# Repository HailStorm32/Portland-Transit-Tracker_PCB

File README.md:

Info
=========
These are the PCB files for the custom PCB that shows in real time what TriMet MAX stations have a train at them. Details regarding the code can be found <a href="https://github.com/HailStorm32/Portland-Transit-Tracker_Code">here</a>. More detail into how this was made, can be found <a href="https://www.vsickle.net/projects/trimet-transit-tracker.html">here</a>

V1 and V2.1 were both designed in Eagle. V2.1 is the version that was actually produced. 

For V2.1, the board was manufactuerd through <a href="https://jlcpcb.com/">JLCPCB</a>, and I solderd all the SMD componets.

## Bill of Materials for V2.1
</img>

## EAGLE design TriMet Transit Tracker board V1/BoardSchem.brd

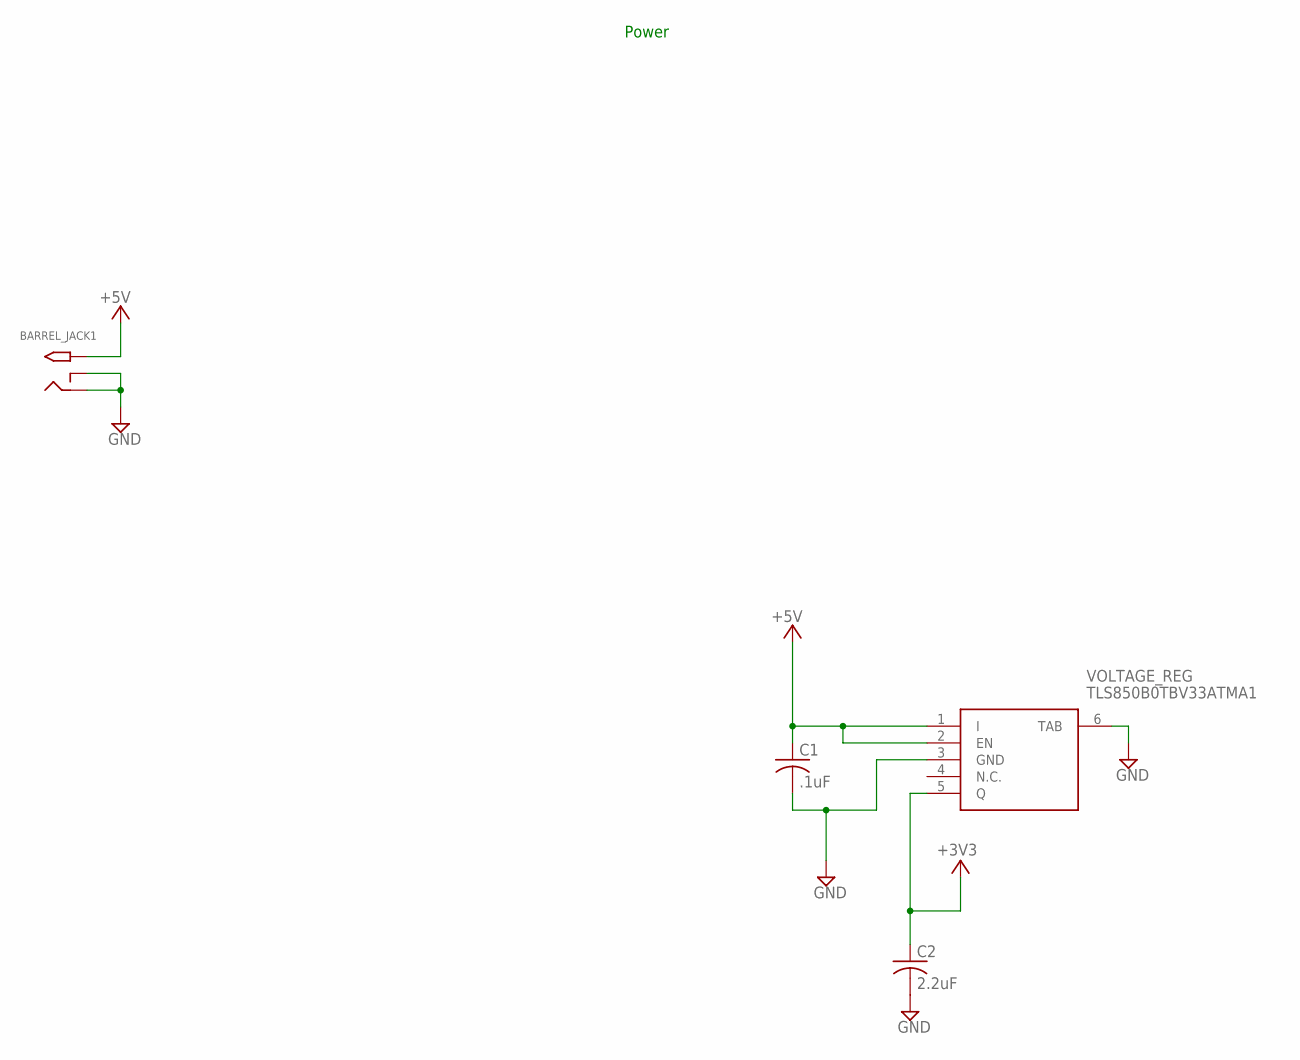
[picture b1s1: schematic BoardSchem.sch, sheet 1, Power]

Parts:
BARREL_JACK1: 2.1MMJACKTHM; PJ-102A
C1: .1uF; C0805
C2: 2.2uF; C0805
VOLTAGE_REG: TLS850B0TBV33ATMA1

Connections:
+3V3: C2.1, VOLTAGE_REG.5 (Q); also elsewhere on the board
+5V: BARREL_JACK1.TIP, C1.1, VOLTAGE_REG.1 (I), VOLTAGE_REG.2 (EN); also elsewhere on the board
GND: BARREL_JACK1.RING, BARREL_JACK1.RING_SW, C1.2, C2.2, VOLTAGE_REG.3 (GND), VOLTAGE_REG.6 (TAB); also elsewhere on the board

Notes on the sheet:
Power

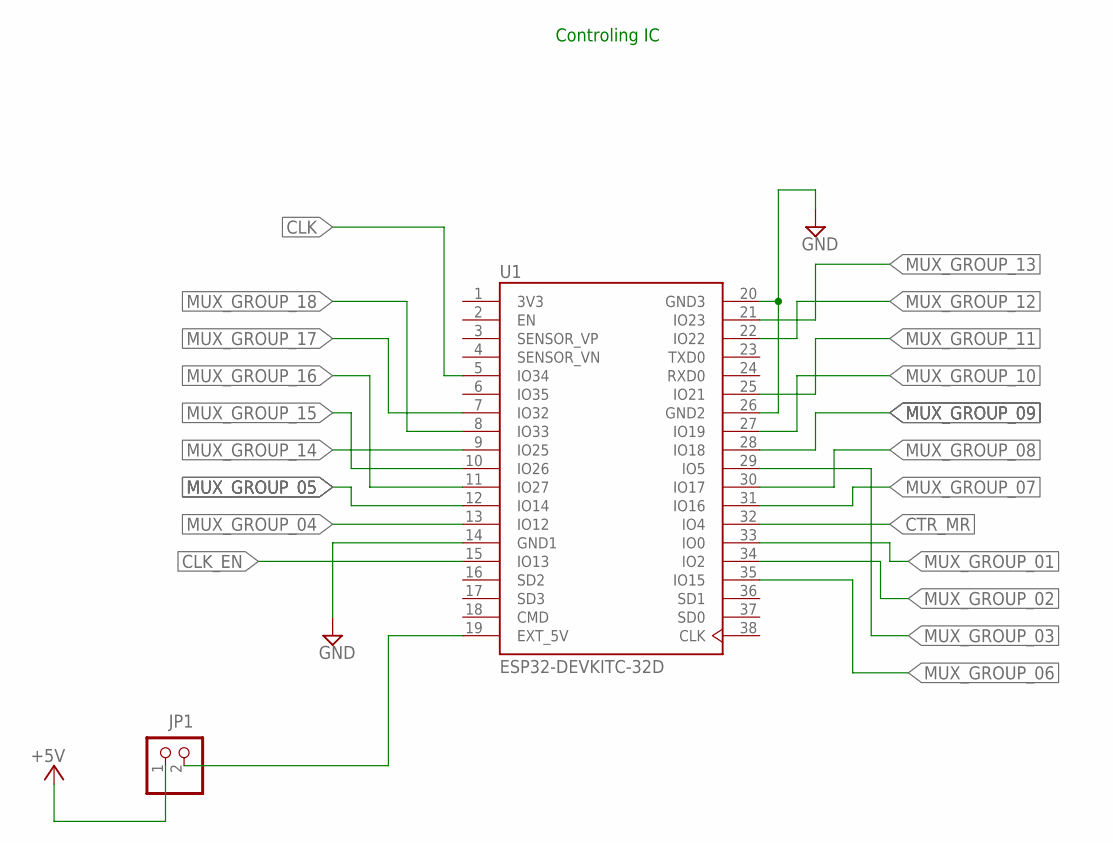
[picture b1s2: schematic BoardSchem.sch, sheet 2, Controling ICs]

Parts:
JP1: PINHD-1X2; 1X02
U1: ESP32-DEVKITC-32D; MODULE_ESP32-DEVKITC-32D

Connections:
3V3: U1.1 (3V3)
+5V: JP1.1; also elsewhere on the board
CLK: U1.5 (IO34); also elsewhere on the board
CLK_EN: U1.15 (IO13); also elsewhere on the board
CTR_MR: U1.32 (IO4); also elsewhere on the board
GND: U1.14 (GND1), U1.20 (GND3), U1.26 (GND2); also elsewhere on the board
MUX_GROUP_01: U1.33 (IO0); also elsewhere on the board
MUX_GROUP_02: U1.34 (IO2); also elsewhere on the board
MUX_GROUP_03: U1.29 (IO5); also elsewhere on the board
MUX_GROUP_04: U1.13 (IO12); also elsewhere on the board
MUX_GROUP_05: U1.12 (IO14); also elsewhere on the board
MUX_GROUP_06: U1.35 (IO15); also elsewhere on the board
MUX_GROUP_07: U1.31 (IO16); also elsewhere on the board
MUX_GROUP_08: U1.30 (IO17); also elsewhere on the board
MUX_GROUP_09: U1.28 (IO18); also elsewhere on the board
MUX_GROUP_10: U1.27 (IO19); also elsewhere on the board
MUX_GROUP_11: U1.25 (IO21); also elsewhere on the board
MUX_GROUP_12: U1.22 (IO22); also elsewhere on the board
MUX_GROUP_13: U1.21 (IO23); also elsewhere on the board
MUX_GROUP_14: U1.9 (IO25); also elsewhere on the board
MUX_GROUP_15: U1.10 (IO26); also elsewhere on the board
MUX_GROUP_16: U1.11 (IO27); also elsewhere on the board
MUX_GROUP_17: U1.7 (IO32); also elsewhere on the board
MUX_GROUP_18: U1.8 (IO33); also elsewhere on the board
unnamed: JP1.2, U1.19 (EXT_5V)

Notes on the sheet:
Controling IC

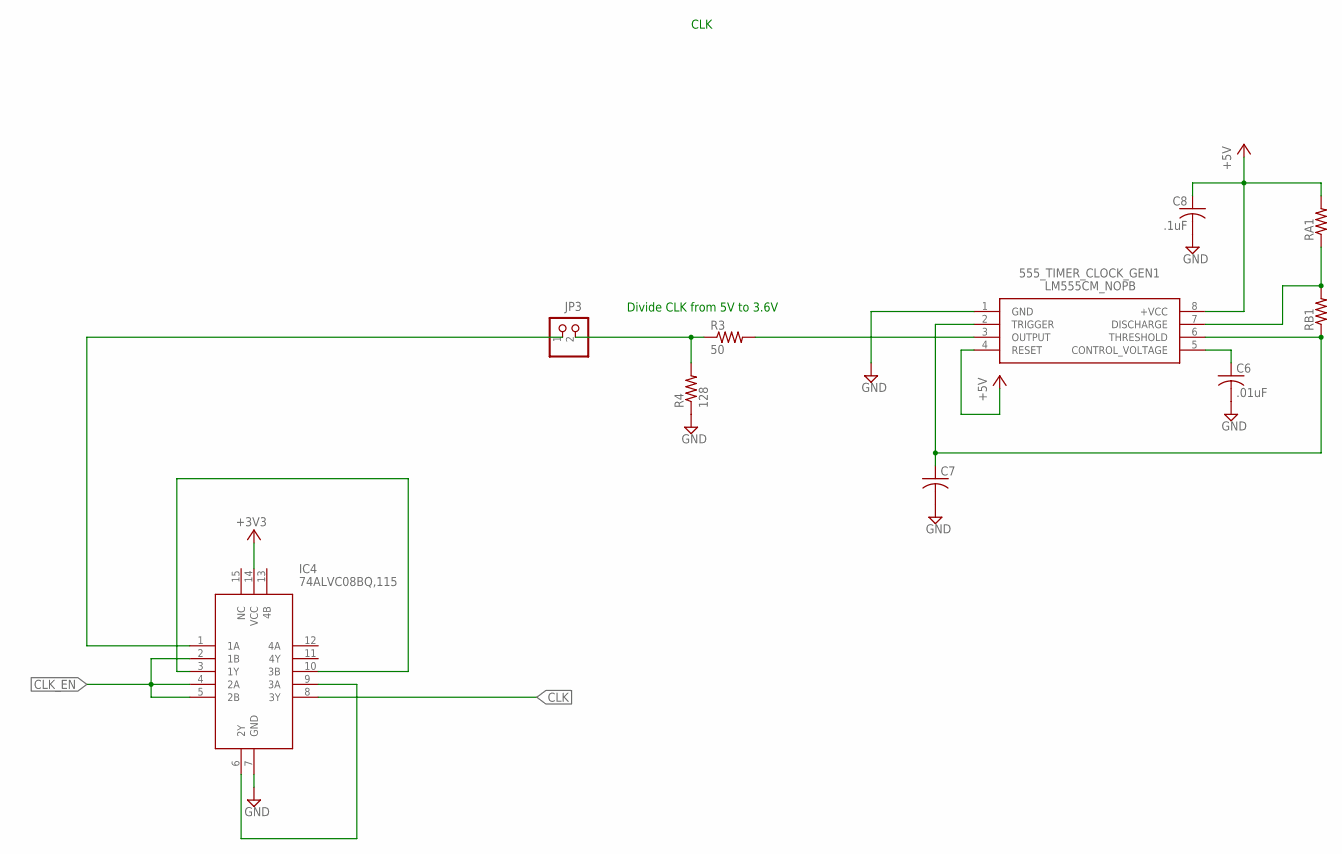
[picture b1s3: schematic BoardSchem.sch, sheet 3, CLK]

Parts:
555_TIMER_CLOCK_GEN1: LM555CM_NOPB; SOIC127P600X175-8N
C6: .01uF; C0805
C7: C-USC0805; C0805
C8: .1uF; C0805
IC4: 74ALVC08BQ,115; QFN50P250X300X100-15N
JP3: PINHD-1X2; 1X02
R3: 50; R0805
R4: 128; R0805
RA1: R-US_R0805; R0805
RB1: R-US_R0805; R0805

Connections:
+3V3: IC4.14 (VCC); also elsewhere on the board
+5V: 555_TIMER_CLOCK_GEN1.4 (RESET), 555_TIMER_CLOCK_GEN1.8 (+VCC), C8.1, RA1.2; also elsewhere on the board
CLK: IC4.8 (3Y); also elsewhere on the board
CLK_EN: IC4.2 (1B), IC4.4 (2A), IC4.5 (2B); also elsewhere on the board
GND: 555_TIMER_CLOCK_GEN1.1 (GND), C6.2, C7.2, C8.2, IC4.7 (GND), R4.1; also elsewhere on the board
unnamed: JP3.2, R3.1, R4.2
unnamed: 555_TIMER_CLOCK_GEN1.5 (CONTROL_VOLTAGE), C6.1
unnamed: 555_TIMER_CLOCK_GEN1.3 (OUTPUT), R3.2
unnamed: 555_TIMER_CLOCK_GEN1.2 (TRIGGER), 555_TIMER_CLOCK_GEN1.6 (THRESHOLD), C7.1, RB1.1
unnamed: 555_TIMER_CLOCK_GEN1.7 (DISCHARGE), RA1.1, RB1.2
unnamed: IC4.1 (1A), JP3.1
unnamed: IC4.6 (2Y), IC4.9 (3A)
unnamed: IC4.3 (1Y), IC4.10 (3B)

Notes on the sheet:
Divide CLK from 5V to 3.6V
CLK

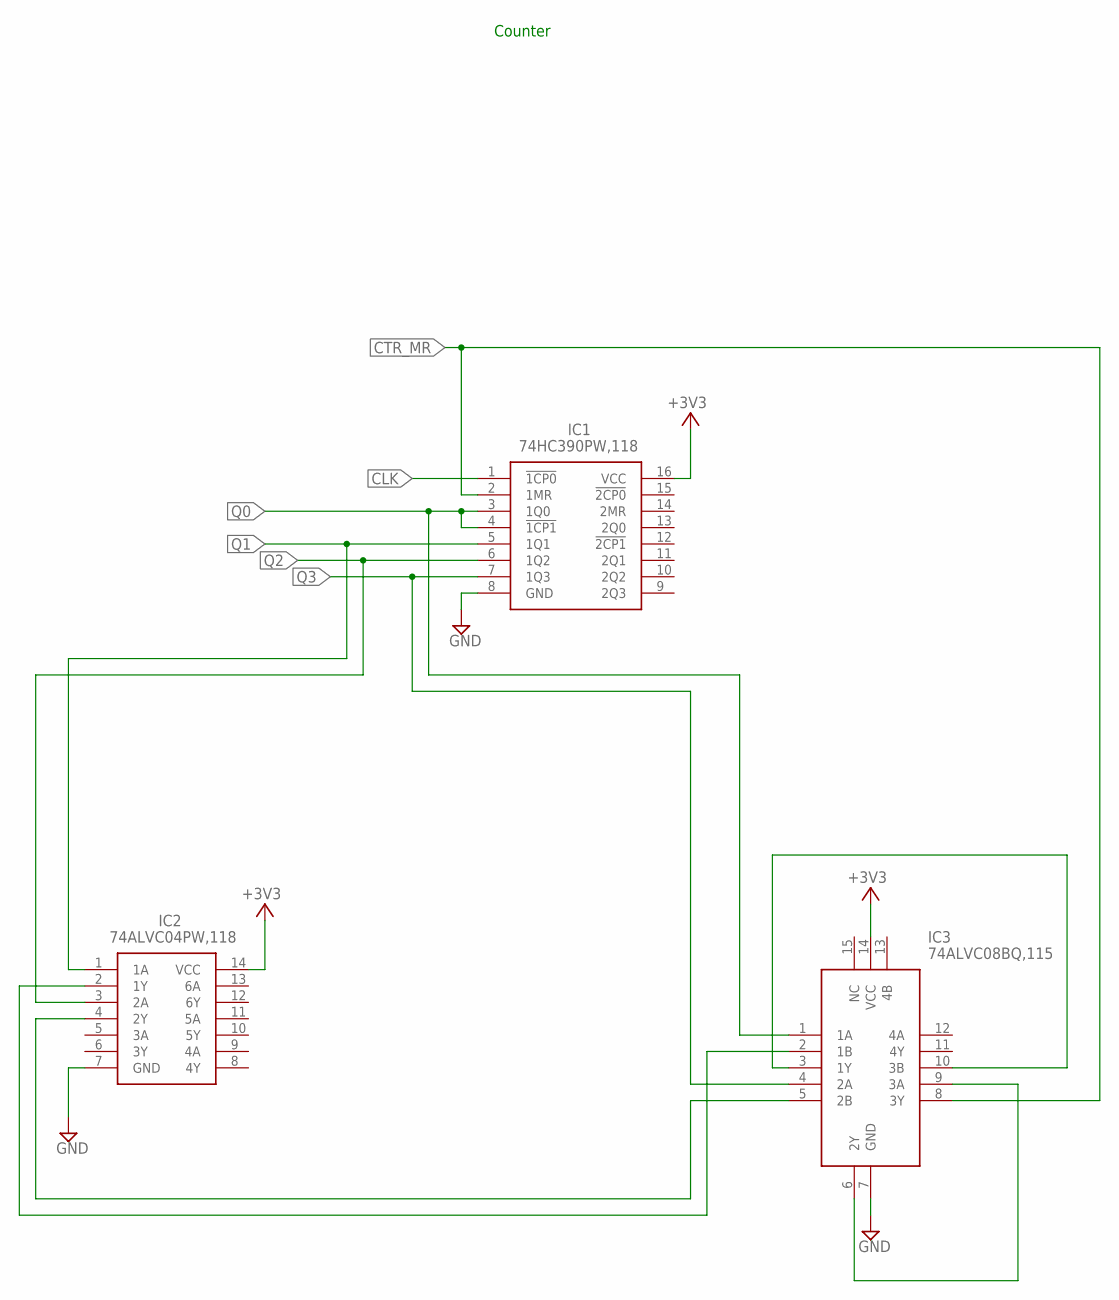
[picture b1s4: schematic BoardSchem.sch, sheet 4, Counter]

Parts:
IC1: 74HC390PW,118; SOP65P640X110-16N
IC2: 74ALVC04PW,118; SOP65P640X110-14N
IC3: 74ALVC08BQ,115; QFN50P250X300X100-15N

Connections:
+3V3: IC1.16 (VCC), IC2.14 (VCC), IC3.14 (VCC); also elsewhere on the board
CLK: IC1.1 (!1CP0); also elsewhere on the board
CTR_MR: IC1.2 (1MR), IC3.8 (3Y); also elsewhere on the board
GND: IC1.8 (GND), IC2.7 (GND), IC3.7 (GND); also elsewhere on the board
unnamed: IC2.4 (2Y), IC3.5 (2B)
unnamed: IC3.3 (1Y), IC3.10 (3B)
unnamed: IC2.2 (1Y), IC3.2 (1B)
unnamed: IC3.6 (2Y), IC3.9 (3A)
Q0: IC1.3 (1Q0), IC1.4 (!1CP1), IC3.1 (1A); also elsewhere on the board
Q1: IC1.5 (1Q1), IC2.1 (1A); also elsewhere on the board
Q2: IC1.6 (1Q2), IC2.3 (2A); also elsewhere on the board
Q3: IC1.7 (1Q3), IC3.4 (2A)

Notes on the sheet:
Counter

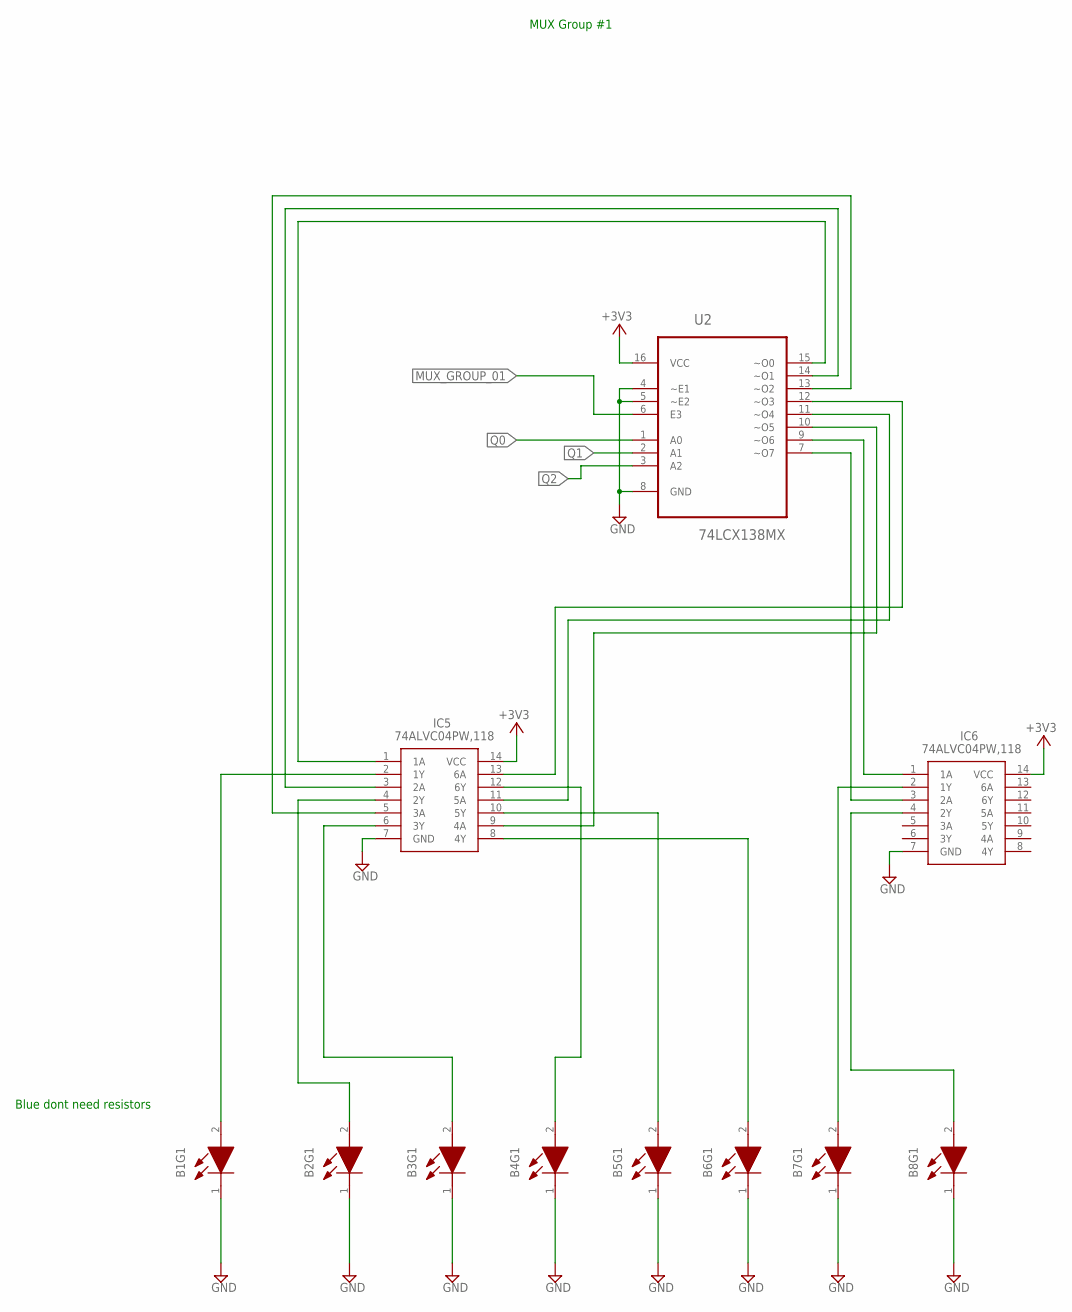
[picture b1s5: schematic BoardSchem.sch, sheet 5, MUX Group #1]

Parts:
B1G1, B2G1, B3G1, B4G1, B5G1, B6G1, B7G1, B8G1: LTST-C170TBKT; LEDC2012X120N
IC5, IC6: 74ALVC04PW,118; SOP65P640X110-14N
U2: 74LCX138MX; SOIC127P600X175-16N

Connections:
+3V3: IC5.14 (VCC), IC6.14 (VCC), U2.16 (VCC); also elsewhere on the board
GND: B1G1.1 (K), B2G1.1 (K), B3G1.1 (K), B4G1.1 (K), B5G1.1 (K), B6G1.1 (K), B7G1.1 (K), B8G1.1 (K), IC5.7 (GND), IC6.7 (GND), U2.4 (~E1), U2.5 (~E2), U2.8 (GND); also elsewhere on the board
MUX_GROUP_01: U2.6 (E3); also elsewhere on the board
unnamed: IC5.1 (1A), U2.15 (~O0)
unnamed: B1G1.2 (A), IC5.2 (1Y)
unnamed: IC5.3 (2A), U2.14 (~O1)
unnamed: B2G1.2 (A), IC5.4 (2Y)
unnamed: IC5.5 (3A), U2.13 (~O2)
unnamed: B3G1.2 (A), IC5.6 (3Y)
unnamed: IC5.13 (6A), U2.12 (~O3)
unnamed: B4G1.2 (A), IC5.12 (6Y)
unnamed: IC5.11 (5A), U2.11 (~O4)
unnamed: B5G1.2 (A), IC5.10 (5Y)
unnamed: IC5.9 (4A), U2.10 (~O5)
unnamed: B6G1.2 (A), IC5.8 (4Y)
unnamed: IC6.1 (1A), U2.9 (~O6)
unnamed: B7G1.2 (A), IC6.2 (1Y)
unnamed: IC6.3 (2A), U2.7 (~O7)
unnamed: B8G1.2 (A), IC6.4 (2Y)
Q0: U2.1 (A0); also elsewhere on the board
Q1: U2.2 (A1); also elsewhere on the board
Q2: U2.3 (A2); also elsewhere on the board

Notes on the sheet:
Blue dont need resistors
MUX Group #1

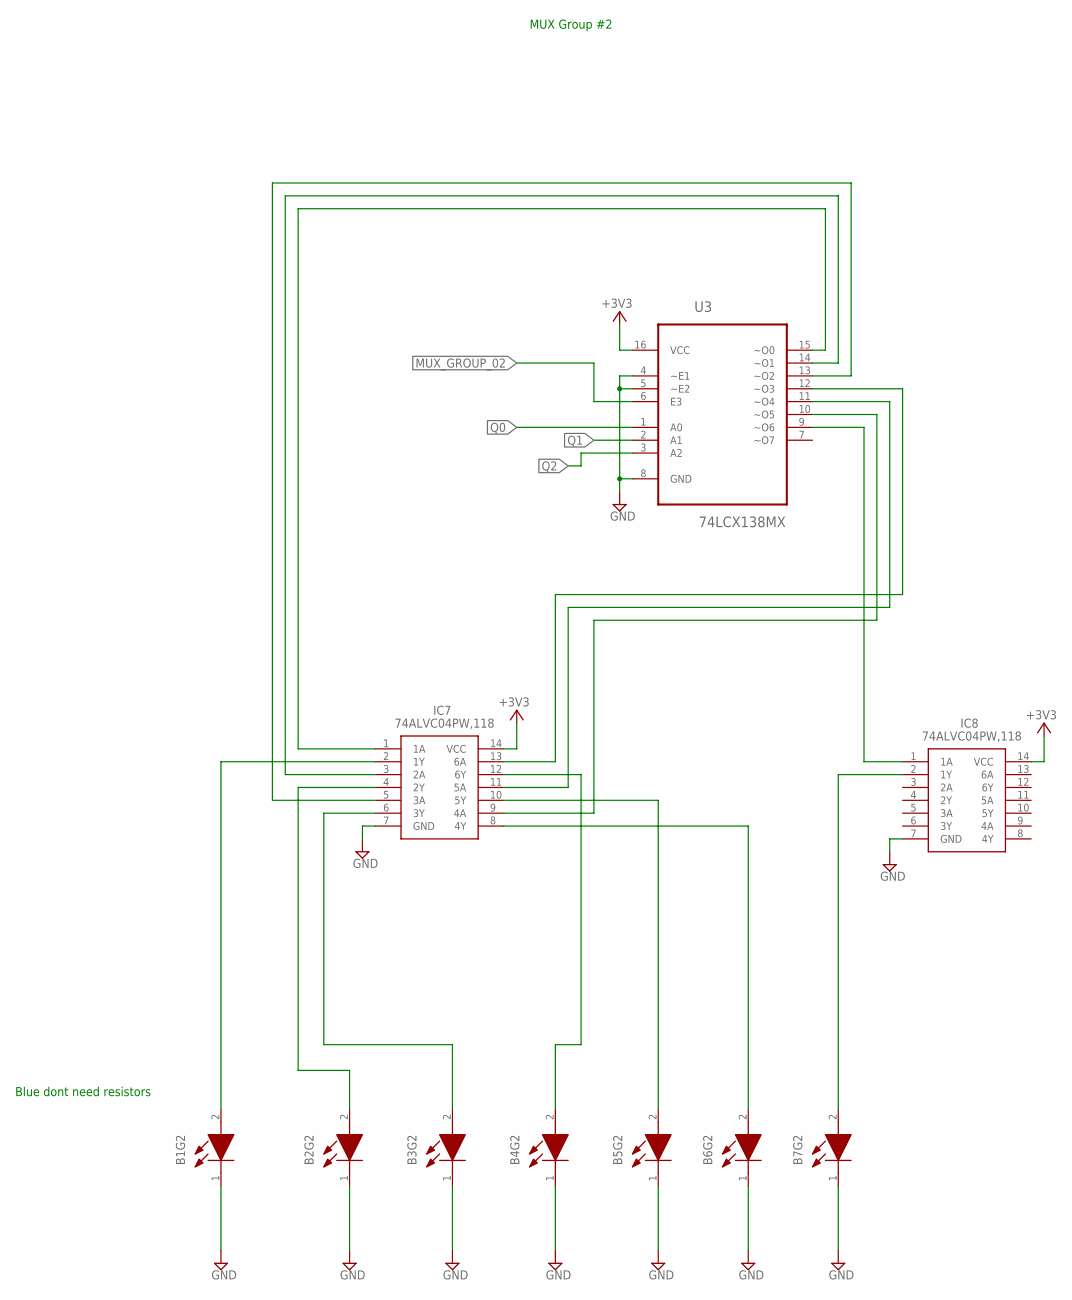
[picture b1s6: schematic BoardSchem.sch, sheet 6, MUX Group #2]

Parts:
B1G2, B2G2, B3G2, B4G2, B5G2, B6G2, B7G2: LTST-C170TBKT; LEDC2012X120N
IC7, IC8: 74ALVC04PW,118; SOP65P640X110-14N
U3: 74LCX138MX; SOIC127P600X175-16N

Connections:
+3V3: IC7.14 (VCC), IC8.14 (VCC), U3.16 (VCC); also elsewhere on the board
GND: B1G2.1 (K), B2G2.1 (K), B3G2.1 (K), B4G2.1 (K), B5G2.1 (K), B6G2.1 (K), B7G2.1 (K), IC7.7 (GND), IC8.7 (GND), U3.4 (~E1), U3.5 (~E2), U3.8 (GND); also elsewhere on the board
MUX_GROUP_02: U3.6 (E3); also elsewhere on the board
unnamed: IC7.1 (1A), U3.15 (~O0)
unnamed: B1G2.2 (A), IC7.2 (1Y)
unnamed: IC7.3 (2A), U3.14 (~O1)
unnamed: B2G2.2 (A), IC7.4 (2Y)
unnamed: IC7.5 (3A), U3.13 (~O2)
unnamed: B3G2.2 (A), IC7.6 (3Y)
unnamed: IC7.13 (6A), U3.12 (~O3)
unnamed: B4G2.2 (A), IC7.12 (6Y)
unnamed: IC7.11 (5A), U3.11 (~O4)
unnamed: B5G2.2 (A), IC7.10 (5Y)
unnamed: IC7.9 (4A), U3.10 (~O5)
unnamed: B6G2.2 (A), IC7.8 (4Y)
unnamed: IC8.1 (1A), U3.9 (~O6)
unnamed: B7G2.2 (A), IC8.2 (1Y)
Q0: U3.1 (A0); also elsewhere on the board
Q1: U3.2 (A1); also elsewhere on the board
Q2: U3.3 (A2); also elsewhere on the board

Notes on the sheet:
Blue dont need resistors
MUX Group #2

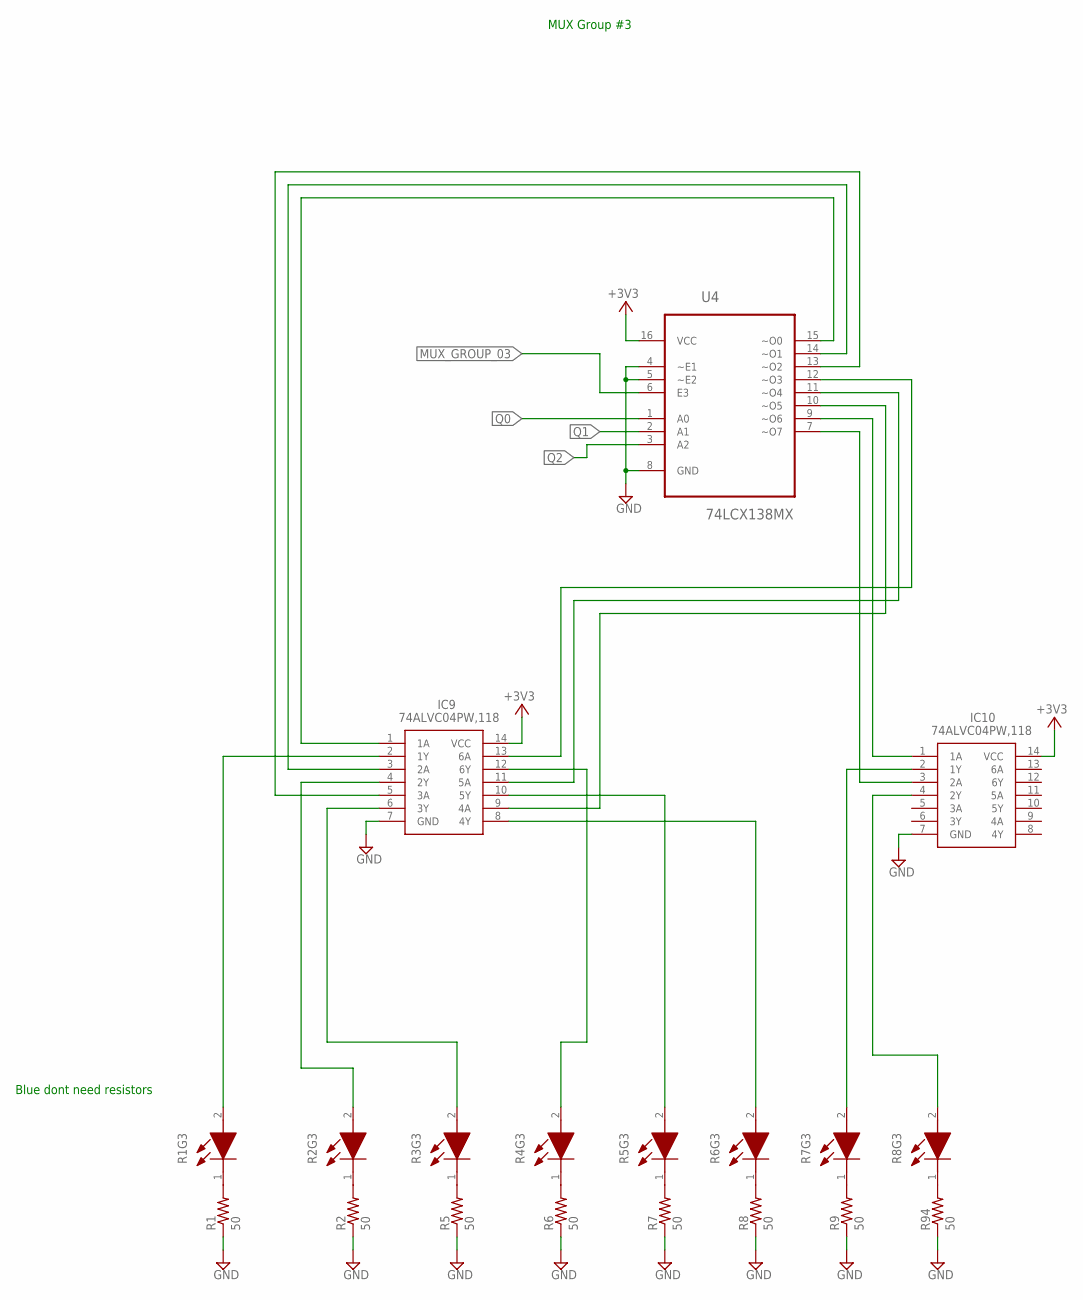
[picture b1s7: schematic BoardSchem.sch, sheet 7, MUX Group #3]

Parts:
IC9, IC10: 74ALVC04PW,118; SOP65P640X110-14N
R1, R2, R5, R6, R7, R8, R9, R94: 50; R0805
R1G3, R2G3, R3G3, R4G3, R5G3, R6G3, R7G3, R8G3: LTST-C170TBKT; LEDC2012X120N
U4: 74LCX138MX; SOIC127P600X175-16N

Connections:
+3V3: IC9.14 (VCC), IC10.14 (VCC), U4.16 (VCC); also elsewhere on the board
GND: IC9.7 (GND), IC10.7 (GND), R1.1, R2.1, R5.1, R6.1, R7.1, R8.1, R9.1, R94.1, U4.4 (~E1), U4.5 (~E2), U4.8 (GND); also elsewhere on the board
MUX_GROUP_03: U4.6 (E3); also elsewhere on the board
unnamed: IC10.3 (2A), U4.7 (~O7)
unnamed: R1.2, R1G3.1 (K)
unnamed: R2.2, R2G3.1 (K)
unnamed: R8G3.1 (K), R94.2
unnamed: IC9.1 (1A), U4.15 (~O0)
unnamed: IC9.2 (1Y), R1G3.2 (A)
unnamed: IC9.3 (2A), U4.14 (~O1)
unnamed: IC9.4 (2Y), R2G3.2 (A)
unnamed: IC9.5 (3A), U4.13 (~O2)
unnamed: IC9.6 (3Y), R3G3.2 (A)
unnamed: IC9.13 (6A), U4.12 (~O3)
unnamed: IC9.12 (6Y), R4G3.2 (A)
unnamed: IC9.11 (5A), U4.11 (~O4)
unnamed: IC9.10 (5Y), R5G3.2 (A)
unnamed: IC9.9 (4A), U4.10 (~O5)
unnamed: IC9.8 (4Y), R6G3.2 (A)
unnamed: IC10.1 (1A), U4.9 (~O6)
unnamed: IC10.2 (1Y), R7G3.2 (A)
unnamed: R3G3.1 (K), R5.2
unnamed: R4G3.1 (K), R6.2
unnamed: IC10.4 (2Y), R8G3.2 (A)
unnamed: R5G3.1 (K), R7.2
unnamed: R6G3.1 (K), R8.2
unnamed: R7G3.1 (K), R9.2
Q0: U4.1 (A0); also elsewhere on the board
Q1: U4.2 (A1); also elsewhere on the board
Q2: U4.3 (A2); also elsewhere on the board

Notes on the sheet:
Blue dont need resistors
MUX Group #3

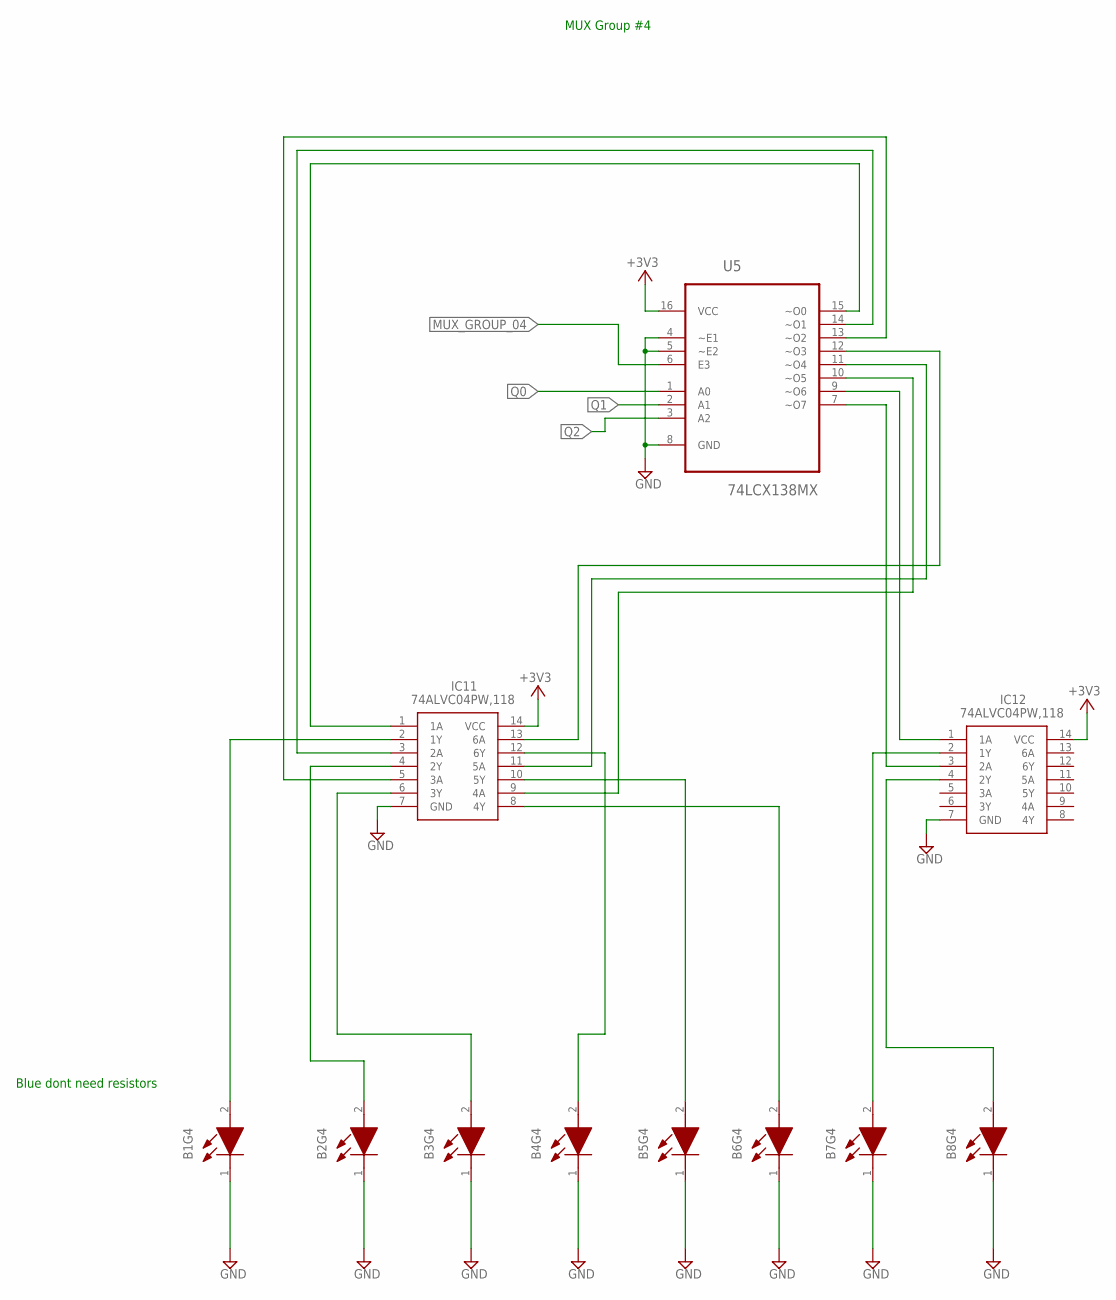
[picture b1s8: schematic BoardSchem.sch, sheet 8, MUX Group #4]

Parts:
B1G4, B2G4, B3G4, B4G4, B5G4, B6G4, B7G4, B8G4: LTST-C170TBKT; LEDC2012X120N
IC11, IC12: 74ALVC04PW,118; SOP65P640X110-14N
U5: 74LCX138MX; SOIC127P600X175-16N

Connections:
+3V3: IC11.14 (VCC), IC12.14 (VCC), U5.16 (VCC); also elsewhere on the board
GND: B1G4.1 (K), B2G4.1 (K), B3G4.1 (K), B4G4.1 (K), B5G4.1 (K), B6G4.1 (K), B7G4.1 (K), B8G4.1 (K), IC11.7 (GND), IC12.7 (GND), U5.4 (~E1), U5.5 (~E2), U5.8 (GND); also elsewhere on the board
MUX_GROUP_04: U5.6 (E3); also elsewhere on the board
unnamed: IC11.1 (1A), U5.15 (~O0)
unnamed: B1G4.2 (A), IC11.2 (1Y)
unnamed: IC11.3 (2A), U5.14 (~O1)
unnamed: B2G4.2 (A), IC11.4 (2Y)
unnamed: IC11.5 (3A), U5.13 (~O2)
unnamed: B3G4.2 (A), IC11.6 (3Y)
unnamed: IC11.13 (6A), U5.12 (~O3)
unnamed: B4G4.2 (A), IC11.12 (6Y)
unnamed: IC11.11 (5A), U5.11 (~O4)
unnamed: B5G4.2 (A), IC11.10 (5Y)
unnamed: IC11.9 (4A), U5.10 (~O5)
unnamed: B6G4.2 (A), IC11.8 (4Y)
unnamed: IC12.1 (1A), U5.9 (~O6)
unnamed: B7G4.2 (A), IC12.2 (1Y)
unnamed: IC12.3 (2A), U5.7 (~O7)
unnamed: B8G4.2 (A), IC12.4 (2Y)
Q0: U5.1 (A0); also elsewhere on the board
Q1: U5.2 (A1); also elsewhere on the board
Q2: U5.3 (A2); also elsewhere on the board

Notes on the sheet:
Blue dont need resistors
MUX Group #4

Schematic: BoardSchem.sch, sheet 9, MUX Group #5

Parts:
B1G5, B2G5, B3G5, B4G5: LTST-C170TBKT; LEDC2012X120N
G6G5, G7G5, G8G5: LTST-C170TBKT; LEDC2012X120N
IC13, IC14: 74ALVC04PW,118; SOP65P640X110-14N
R5G5: LTST-C170TBKT; LEDC2012X120N
R10, R11, R12, R13: 50; R0805
U6: 74LCX138MX; SOIC127P600X175-16N

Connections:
+3V3: IC13.14 (VCC), IC14.14 (VCC), U6.16 (VCC); also elsewhere on the board
GND: B1G5.1 (K), B2G5.1 (K), B3G5.1 (K), B4G5.1 (K), IC13.7 (GND), IC14.7 (GND), R10.1, R11.1, R12.1, R13.1, U6.4 (~E1), U6.5 (~E2), U6.8 (GND); also elsewhere on the board
MUX_GROUP_05: U6.6 (E3); also elsewhere on the board
unnamed: IC13.1 (1A), U6.15 (~O0)
unnamed: B1G5.2 (A), IC13.2 (1Y)
unnamed: IC13.3 (2A), U6.14 (~O1)
unnamed: B2G5.2 (A), IC13.4 (2Y)
unnamed: IC13.5 (3A), U6.13 (~O2)
unnamed: B3G5.2 (A), IC13.6 (3Y)
unnamed: IC13.13 (6A), U6.12 (~O3)
unnamed: B4G5.2 (A), IC13.12 (6Y)
unnamed: IC13.11 (5A), U6.11 (~O4)
unnamed: IC13.10 (5Y), R5G5.2 (A)
unnamed: IC13.9 (4A), U6.10 (~O5)
unnamed: G6G5.2 (A), IC13.8 (4Y)
unnamed: IC14.1 (1A), U6.9 (~O6)
unnamed: G7G5.2 (A), IC14.2 (1Y)
unnamed: IC14.3 (2A), U6.7 (~O7)
unnamed: G8G5.2 (A), IC14.4 (2Y)
unnamed: R5G5.1 (K), R10.2
unnamed: G6G5.1 (K), R11.2
unnamed: G7G5.1 (K), R12.2
unnamed: G8G5.1 (K), R13.2
Q0: U6.1 (A0); also elsewhere on the board
Q1: U6.2 (A1); also elsewhere on the board
Q2: U6.3 (A2); also elsewhere on the board

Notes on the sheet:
Blue dont need resistors
MUX Group #5

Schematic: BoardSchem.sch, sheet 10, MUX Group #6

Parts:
IC15, IC16: 74ALVC04PW,118; SOP65P640X110-14N
R1G6, R2G6, R3G6, R4G6, R5G6, R6G6, R7G6, R8G6: LTST-C170TBKT; LEDC2012X120N
R14, R15, R16, R17, R18, R19, R20, R21: 50; R0805
U7: 74LCX138MX; SOIC127P600X175-16N

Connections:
+3V3: IC15.14 (VCC), IC16.14 (VCC), U7.16 (VCC); also elsewhere on the board
GND: IC15.7 (GND), IC16.7 (GND), R14.1, R15.1, R16.1, R17.1, R18.1, R19.1, R20.1, R21.1, U7.4 (~E1), U7.5 (~E2), U7.8 (GND); also elsewhere on the board
MUX_GROUP_06: U7.6 (E3); also elsewhere on the board
unnamed: IC15.1 (1A), U7.15 (~O0)
unnamed: IC15.2 (1Y), R1G6.2 (A)
unnamed: IC15.3 (2A), U7.14 (~O1)
unnamed: IC15.4 (2Y), R2G6.2 (A)
unnamed: IC15.5 (3A), U7.13 (~O2)
unnamed: IC15.6 (3Y), R3G6.2 (A)
unnamed: IC15.13 (6A), U7.12 (~O3)
unnamed: IC15.12 (6Y), R4G6.2 (A)
unnamed: IC15.11 (5A), U7.11 (~O4)
unnamed: IC15.10 (5Y), R5G6.2 (A)
unnamed: IC15.9 (4A), U7.10 (~O5)
unnamed: IC15.8 (4Y), R6G6.2 (A)
unnamed: IC16.1 (1A), U7.9 (~O6)
unnamed: IC16.2 (1Y), R7G6.2 (A)
unnamed: IC16.3 (2A), U7.7 (~O7)
unnamed: IC16.4 (2Y), R8G6.2 (A)
unnamed: R1G6.1 (K), R14.2
unnamed: R2G6.1 (K), R15.2
unnamed: R3G6.1 (K), R16.2
unnamed: R4G6.1 (K), R17.2
unnamed: R5G6.1 (K), R18.2
unnamed: R6G6.1 (K), R19.2
unnamed: R7G6.1 (K), R20.2
unnamed: R8G6.1 (K), R21.2
Q0: U7.1 (A0); also elsewhere on the board
Q1: U7.2 (A1); also elsewhere on the board
Q2: U7.3 (A2); also elsewhere on the board

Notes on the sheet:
Blue dont need resistors
MUX Group #6

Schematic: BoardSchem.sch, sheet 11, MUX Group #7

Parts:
G1G7, G2G7, G3G7, G4G7, G7G7: LTST-C170TBKT; LEDC2012X120N
IC17, IC18: 74ALVC04PW,118; SOP65P640X110-14N
O6G7: LTST-C170TBKT; LEDC2012X120N
R22, R23, R24, R25, R26, R27, R28, R29: 50; R0805
U8: 74LCX138MX; SOIC127P600X175-16N
Y5G7, Y8G7: LTST-C170TBKT; LEDC2012X120N

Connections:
+3V3: IC17.14 (VCC), IC18.14 (VCC), U8.16 (VCC); also elsewhere on the board
GND: IC17.7 (GND), IC18.7 (GND), R22.1, R23.1, R24.1, R25.1, R26.1, R27.1, R28.1, R29.1, U8.4 (~E1), U8.5 (~E2), U8.8 (GND); also elsewhere on the board
MUX_GROUP_07: U8.6 (E3); also elsewhere on the board
unnamed: IC17.1 (1A), U8.15 (~O0)
unnamed: G1G7.2 (A), IC17.2 (1Y)
unnamed: IC17.3 (2A), U8.14 (~O1)
unnamed: G2G7.2 (A), IC17.4 (2Y)
unnamed: IC17.5 (3A), U8.13 (~O2)
unnamed: G3G7.2 (A), IC17.6 (3Y)
unnamed: IC17.13 (6A), U8.12 (~O3)
unnamed: G4G7.2 (A), IC17.12 (6Y)
unnamed: IC17.11 (5A), U8.11 (~O4)
unnamed: IC17.10 (5Y), Y5G7.2 (A)
unnamed: IC17.9 (4A), U8.10 (~O5)
unnamed: IC17.8 (4Y), O6G7.2 (A)
unnamed: IC18.1 (1A), U8.9 (~O6)
unnamed: G7G7.2 (A), IC18.2 (1Y)
unnamed: IC18.3 (2A), U8.7 (~O7)
unnamed: IC18.4 (2Y), Y8G7.2 (A)
unnamed: G1G7.1 (K), R22.2
unnamed: G2G7.1 (K), R23.2
unnamed: G3G7.1 (K), R24.2
unnamed: G4G7.1 (K), R25.2
unnamed: R26.2, Y5G7.1 (K)
unnamed: O6G7.1 (K), R27.2
unnamed: G7G7.1 (K), R28.2
unnamed: R29.2, Y8G7.1 (K)
Q0: U8.1 (A0); also elsewhere on the board
Q1: U8.2 (A1); also elsewhere on the board
Q2: U8.3 (A2); also elsewhere on the board

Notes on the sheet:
Blue dont need resistors
MUX Group #7

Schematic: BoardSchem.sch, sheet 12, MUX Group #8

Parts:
G1G8, G2G8, G3G8, G4G8, G5G8, G7G8: LTST-C170TBKT; LEDC2012X120N
IC19, IC20: 74ALVC04PW,118; SOP65P640X110-14N
R30, R31, R32, R33, R34, R35, R36, R37: 50; R0805
U9: 74LCX138MX; SOIC127P600X175-16N
Y6G8, Y8G8: LTST-C170TBKT; LEDC2012X120N

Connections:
+3V3: IC19.14 (VCC), IC20.14 (VCC), U9.16 (VCC); also elsewhere on the board
GND: IC19.7 (GND), IC20.7 (GND), R30.1, R31.1, R32.1, R33.1, R34.1, R35.1, R36.1, R37.1, U9.4 (~E1), U9.5 (~E2), U9.8 (GND); also elsewhere on the board
MUX_GROUP_08: U9.6 (E3); also elsewhere on the board
unnamed: IC19.1 (1A), U9.15 (~O0)
unnamed: G1G8.2 (A), IC19.2 (1Y)
unnamed: IC19.3 (2A), U9.14 (~O1)
unnamed: G2G8.2 (A), IC19.4 (2Y)
unnamed: IC19.5 (3A), U9.13 (~O2)
unnamed: G3G8.2 (A), IC19.6 (3Y)
unnamed: IC19.13 (6A), U9.12 (~O3)
unnamed: G4G8.2 (A), IC19.12 (6Y)
unnamed: IC19.11 (5A), U9.11 (~O4)
unnamed: G5G8.2 (A), IC19.10 (5Y)
unnamed: IC19.9 (4A), U9.10 (~O5)
unnamed: IC19.8 (4Y), Y6G8.2 (A)
unnamed: IC20.1 (1A), U9.9 (~O6)
unnamed: G7G8.2 (A), IC20.2 (1Y)
unnamed: IC20.3 (2A), U9.7 (~O7)
unnamed: IC20.4 (2Y), Y8G8.2 (A)
unnamed: G1G8.1 (K), R30.2
unnamed: G2G8.1 (K), R31.2
unnamed: G3G8.1 (K), R32.2
unnamed: G4G8.1 (K), R33.2
unnamed: G5G8.1 (K), R34.2
unnamed: R35.2, Y6G8.1 (K)
unnamed: G7G8.1 (K), R36.2
unnamed: R37.2, Y8G8.1 (K)
Q0: U9.1 (A0); also elsewhere on the board
Q1: U9.2 (A1); also elsewhere on the board
Q2: U9.3 (A2); also elsewhere on the board

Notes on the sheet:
Blue dont need resistors
MUX Group #8

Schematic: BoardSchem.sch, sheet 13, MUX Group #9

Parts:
IC21, IC22: 74ALVC04PW,118; SOP65P640X110-14N
O1G9, O2G9, O3G9, O4G9, O5G9, O6G9, O7G9, O8G9: LTST-C170TBKT; LEDC2012X120N
R38, R39, R40, R41, R42, R43, R44, R45: 50; R0805
U10: 74LCX138MX; SOIC127P600X175-16N

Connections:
+3V3: IC21.14 (VCC), IC22.14 (VCC), U10.16 (VCC); also elsewhere on the board
GND: IC21.7 (GND), IC22.7 (GND), R38.1, R39.1, R40.1, R41.1, R42.1, R43.1, R44.1, R45.1, U10.4 (~E1), U10.5 (~E2), U10.8 (GND); also elsewhere on the board
MUX_GROUP_09: U10.6 (E3); also elsewhere on the board
unnamed: IC21.1 (1A), U10.15 (~O0)
unnamed: IC21.2 (1Y), O1G9.2 (A)
unnamed: IC21.3 (2A), U10.14 (~O1)
unnamed: IC21.4 (2Y), O2G9.2 (A)
unnamed: IC21.5 (3A), U10.13 (~O2)
unnamed: IC21.6 (3Y), O3G9.2 (A)
unnamed: IC21.13 (6A), U10.12 (~O3)
unnamed: IC21.12 (6Y), O4G9.2 (A)
unnamed: IC21.11 (5A), U10.11 (~O4)
unnamed: IC21.10 (5Y), O5G9.2 (A)
unnamed: IC21.9 (4A), U10.10 (~O5)
unnamed: IC21.8 (4Y), O6G9.2 (A)
unnamed: IC22.1 (1A), U10.9 (~O6)
unnamed: IC22.2 (1Y), O7G9.2 (A)
unnamed: IC22.3 (2A), U10.7 (~O7)
unnamed: IC22.4 (2Y), O8G9.2 (A)
unnamed: O1G9.1 (K), R38.2
unnamed: O2G9.1 (K), R39.2
unnamed: O3G9.1 (K), R40.2
unnamed: O4G9.1 (K), R41.2
unnamed: O5G9.1 (K), R42.2
unnamed: O7G9.1 (K), R44.2
unnamed: O8G9.1 (K), R45.2
unnamed: O6G9.1 (K), R43.2
Q0: U10.1 (A0); also elsewhere on the board
Q1: U10.2 (A1); also elsewhere on the board
Q2: U10.3 (A2); also elsewhere on the board

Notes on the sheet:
Blue dont need resistors
MUX Group #9

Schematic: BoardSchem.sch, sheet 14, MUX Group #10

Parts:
IC23: 74ALVC04PW,118; SOP65P640X110-14N
R46, R47, R48, R49, R50: 50; R0805
U11: 74LCX138MX; SOIC127P600X175-16N
Y1G10, Y2G10, Y3G10, Y4G10, Y5G10: LTST-C170TBKT; LEDC2012X120N

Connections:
+3V3: IC23.14 (VCC), U11.16 (VCC); also elsewhere on the board
GND: IC23.7 (GND), R46.1, R47.1, R48.1, R49.1, R50.1, U11.4 (~E1), U11.5 (~E2), U11.8 (GND); also elsewhere on the board
MUX_GROUP_10: U11.6 (E3); also elsewhere on the board
unnamed: IC23.1 (1A), U11.15 (~O0)
unnamed: IC23.2 (1Y), Y1G10.2 (A)
unnamed: IC23.3 (2A), U11.14 (~O1)
unnamed: IC23.4 (2Y), Y2G10.2 (A)
unnamed: IC23.5 (3A), U11.13 (~O2)
unnamed: IC23.6 (3Y), Y3G10.2 (A)
unnamed: IC23.13 (6A), U11.12 (~O3)
unnamed: IC23.12 (6Y), Y4G10.2 (A)
unnamed: IC23.11 (5A), U11.11 (~O4)
unnamed: IC23.10 (5Y), Y5G10.2 (A)
unnamed: R46.2, Y1G10.1 (K)
unnamed: R47.2, Y2G10.1 (K)
unnamed: R48.2, Y3G10.1 (K)
unnamed: R49.2, Y4G10.1 (K)
unnamed: R50.2, Y5G10.1 (K)
Q0: U11.1 (A0); also elsewhere on the board
Q1: U11.2 (A1); also elsewhere on the board
Q2: U11.3 (A2); also elsewhere on the board

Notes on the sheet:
Blue dont need resistors
MUX Group #10

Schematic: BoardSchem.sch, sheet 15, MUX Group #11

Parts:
IC25, IC26: 74ALVC04PW,118; SOP65P640X110-14N
O1G11, O2G11, O3G11, O4G11, O5G11, O6G11, O7G11, O8G11: LTST-C170TBKT; LEDC2012X120N
R52, R53, R54, R55, R56, R57, R58, R59: 50; R0805
U12: 74LCX138MX; SOIC127P600X175-16N

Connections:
+3V3: IC25.14 (VCC), IC26.14 (VCC), U12.16 (VCC); also elsewhere on the board
GND: IC25.7 (GND), IC26.7 (GND), R52.1, R53.1, R54.1, R55.1, R56.1, R57.1, R58.1, R59.1, U12.4 (~E1), U12.5 (~E2), U12.8 (GND); also elsewhere on the board
MUX_GROUP_11: U12.6 (E3); also elsewhere on the board
unnamed: IC25.1 (1A), U12.15 (~O0)
unnamed: IC25.2 (1Y), O1G11.2 (A)
unnamed: IC25.3 (2A), U12.14 (~O1)
unnamed: IC25.4 (2Y), O2G11.2 (A)
unnamed: IC25.5 (3A), U12.13 (~O2)
unnamed: IC25.6 (3Y), O3G11.2 (A)
unnamed: IC25.13 (6A), U12.12 (~O3)
unnamed: IC25.12 (6Y), O4G11.2 (A)
unnamed: IC25.11 (5A), U12.11 (~O4)
unnamed: IC25.10 (5Y), O5G11.2 (A)
unnamed: IC25.9 (4A), U12.10 (~O5)
unnamed: IC25.8 (4Y), O6G11.2 (A)
unnamed: IC26.1 (1A), U12.9 (~O6)
unnamed: IC26.2 (1Y), O7G11.2 (A)
unnamed: IC26.3 (2A), U12.7 (~O7)
unnamed: IC26.4 (2Y), O8G11.2 (A)
unnamed: O1G11.1 (K), R52.2
unnamed: O2G11.1 (K), R53.2
unnamed: O3G11.1 (K), R54.2
unnamed: O4G11.1 (K), R55.2
unnamed: O5G11.1 (K), R56.2
unnamed: O6G11.1 (K), R57.2
unnamed: O7G11.1 (K), R58.2
unnamed: O8G11.1 (K), R59.2
Q0: U12.1 (A0); also elsewhere on the board
Q1: U12.2 (A1); also elsewhere on the board
Q2: U12.3 (A2); also elsewhere on the board

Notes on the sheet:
Blue dont need resistors
MUX Group #11
